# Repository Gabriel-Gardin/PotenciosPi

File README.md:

# PotenciosPi
PotenciosPi is a low cost Raspberry Pi based potenciostat. 

It uses an 12 bit ADC/DAC converter from: https://uk.pi-supply.com/products/adc-dac-pi-zero.

Schematics and the board is available at pcb folder.

To use it, install any version of Raspbian on your raspberry Pi 3 and execute Potenciostato.py

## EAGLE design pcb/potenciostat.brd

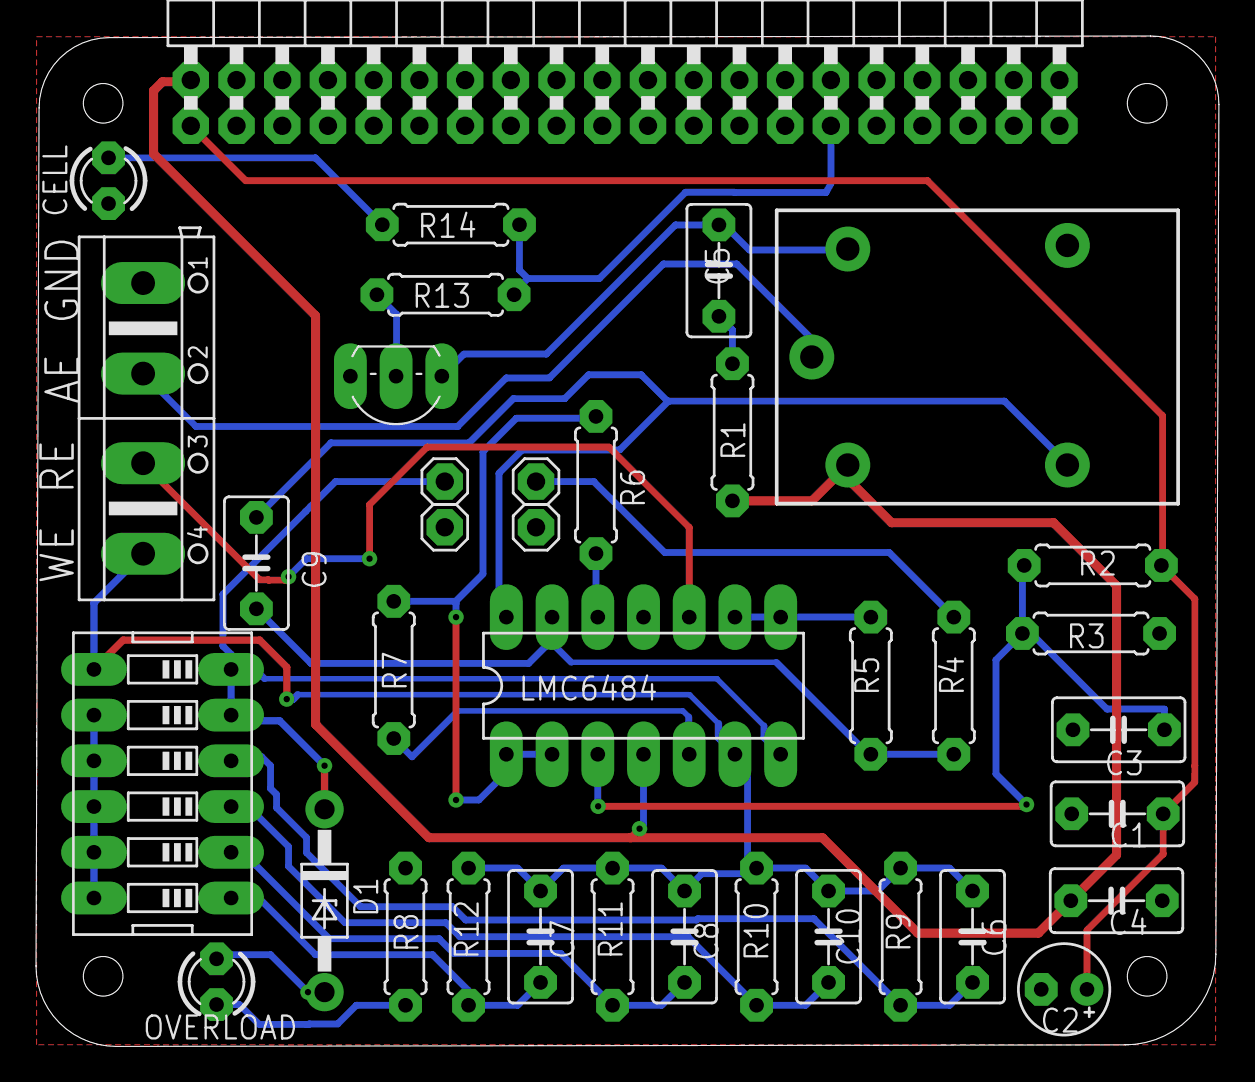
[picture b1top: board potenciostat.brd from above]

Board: 2 copper layers, 65.7 x 56.1 mm, 37 parts (0 on the bottom side), 27 nets.

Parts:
C1, C3, C4: 100nf; C050-035X075
C2: 1uF; E2,5-5
C5: ?; C050-035X075
C6, C7, C8, C10: 1uF; C050-035X075
C9: 1nf; C050-035X075
CELL: LED3MM
D1: 1N4728; DO41Z10
JP1: 2X20/90
JP2, JP3, JP4, JP5: 1X01
K2: ZNS5406; ZN5
LMC6484: TL074P; DIL14
OVERLOAD: Overload; LED3MM
Q1: BC548; TO92-EBC
R1: ?; 0207/7
R2, R3, R4, R5: 10K; 0207/7
R6, R7, R11: 4K7; 0207/7
R8: 1k; 0207/7
R9: 470K; 0207/7
R10: 47K; 0207/7
R12: 470; 0207/7
R13: 560R; 0207/7
R14: 1K; 0207/7
SW1: EDG-06
X1: AK500/4

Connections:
3V3: C1.1, C2.+, JP1.1, R2.2
5V: C4.1, JP1.2, K2.A1, LMC6484.4, R1.2
AD: D1.C, JP4.1, LMC6484.7, SW1.5, SW1.6
AUX: C9.2, K2.14, LMC6484.14
AUXEL: K2.11, X1.2
DA: JP2.1, R4.2
GND: C1.2, C2.-, C3.2, C4.2, CELL.K, JP1.25, JP1.39, JP3.1, JP5.1, LMC6484.11, Q1.E, R3.1, R8.1, X1.1
GPIO: JP1.29, R13.1, R14.1
unnamed: OVERLOAD.A, R8.2
unnamed: LMC6484.8, LMC6484.9, R5.2
unnamed: C3.1, LMC6484.3, R2.1, R3.2
unnamed: C9.1, LMC6484.13, R4.1, R5.1
unnamed: C5.1, R1.1
unnamed: LMC6484.12, R6.2
unnamed: C7.2, R12.1, SW1.1
unnamed: LMC6484.5, R7.2
unnamed: SW1.8, SW1.9, SW1.10, SW1.11, SW1.12
unnamed: D1.A, OVERLOAD.K
unnamed: C8.2, R11.1, SW1.2
unnamed: C10.2, R10.1, SW1.3
unnamed: C6.2, R9.1, SW1.4
unnamed: C5.2, K2.A2, Q1.C
unnamed: CELL.A, R14.2
unnamed: Q1.B, R13.2
REFEL: LMC6484.10, X1.3
VCC/2: LMC6484.1, LMC6484.2, R6.1, R7.1
WEL: C6.1, C7.1, C8.1, C10.1, LMC6484.6, R9.2, R10.2, R11.2, R12.2, SW1.7, X1.4

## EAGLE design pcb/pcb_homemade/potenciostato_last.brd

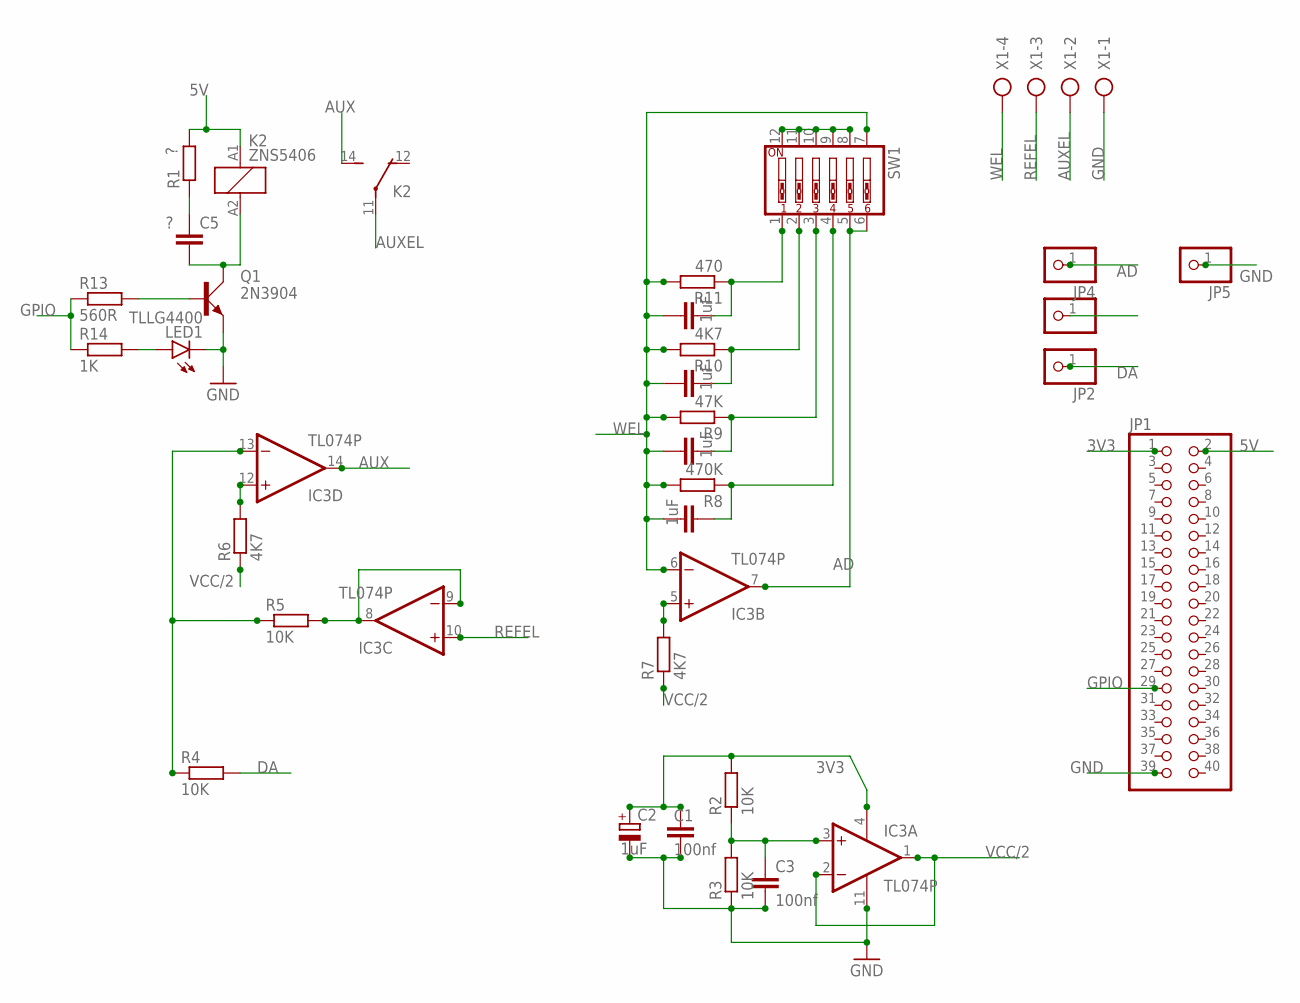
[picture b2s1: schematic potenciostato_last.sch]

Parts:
C1, C3: 100nf; C050-035X075
C2: 1uF; E2,5-5
C4, C6, C7, C8: 1uF; C050-035X075
C5: ?; C050-035X075
IC3: TL074P; DIL14
JP1: PINHD-2X20/90; 2X20/90
JP2, JP3, JP4, JP5: PINHD-1X1; 1X01
K2: ZNS5406; ZN5
LED1: TLLG4400; LED3MM
Q1: 2N3904; TO92D
R1: ?; 0207/7
R2, R3, R4, R5: 10K; 0207/7
R6, R7, R10: 4K7; 0207/7
R8: 470K; 0207/7
R9: 47K; 0207/7
R11: 470; 0207/7
R13: 560R; 0207/7
R14: 1K; 0207/7
SW1: SW_DIP-6; EDG-06
X1: AK500/4

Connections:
3V3: C1.1, C2.+, IC3.4 (V+), JP1.1, R2.2
5V: JP1.2, K2.A1 (1), R1.2
AD: IC3.7 (OUT), JP4.1, SW1.5, SW1.6
AUX: IC3.14 (OUT), K2.14 (S)
AUXEL: K2.11, X1.2
DA: JP2.1, R4.2
GND: C1.2, C2.-, C3.2, IC3.11 (V-), JP1.39, JP5.1, LED1.K (C), Q1.E, R3.1, X1.1
GPIO: JP1.29, R13.1, R14.1
unnamed: C4.2, R8.1, SW1.4
unnamed: IC3.8 (OUT), IC3.9 (-IN), R5.2
unnamed: C3.1, IC3.3 (+IN), R2.1, R3.2
unnamed: IC3.13 (-IN), R4.1, R5.1
unnamed: C5.1, R1.1
unnamed: IC3.12 (+IN), R6.2
unnamed: IC3.5 (+IN), R7.2
unnamed: SW1.8, SW1.9, SW1.10, SW1.11, SW1.12
unnamed: C6.2, R11.1, SW1.1
unnamed: C7.2, R10.1, SW1.2
unnamed: C8.2, R9.1, SW1.3
unnamed: C5.2, K2.A2 (2), Q1.C
unnamed: LED1.A, R14.2
unnamed: Q1.B, R13.2
REFEL: IC3.10 (+IN), X1.3
VCC/2: IC3.1 (OUT), IC3.2 (-IN), R6.1, R7.1
WEL: C4.1, C6.1, C7.1, C8.1, IC3.6 (-IN), R8.2, R9.2, R10.2, R11.2, SW1.7, X1.4

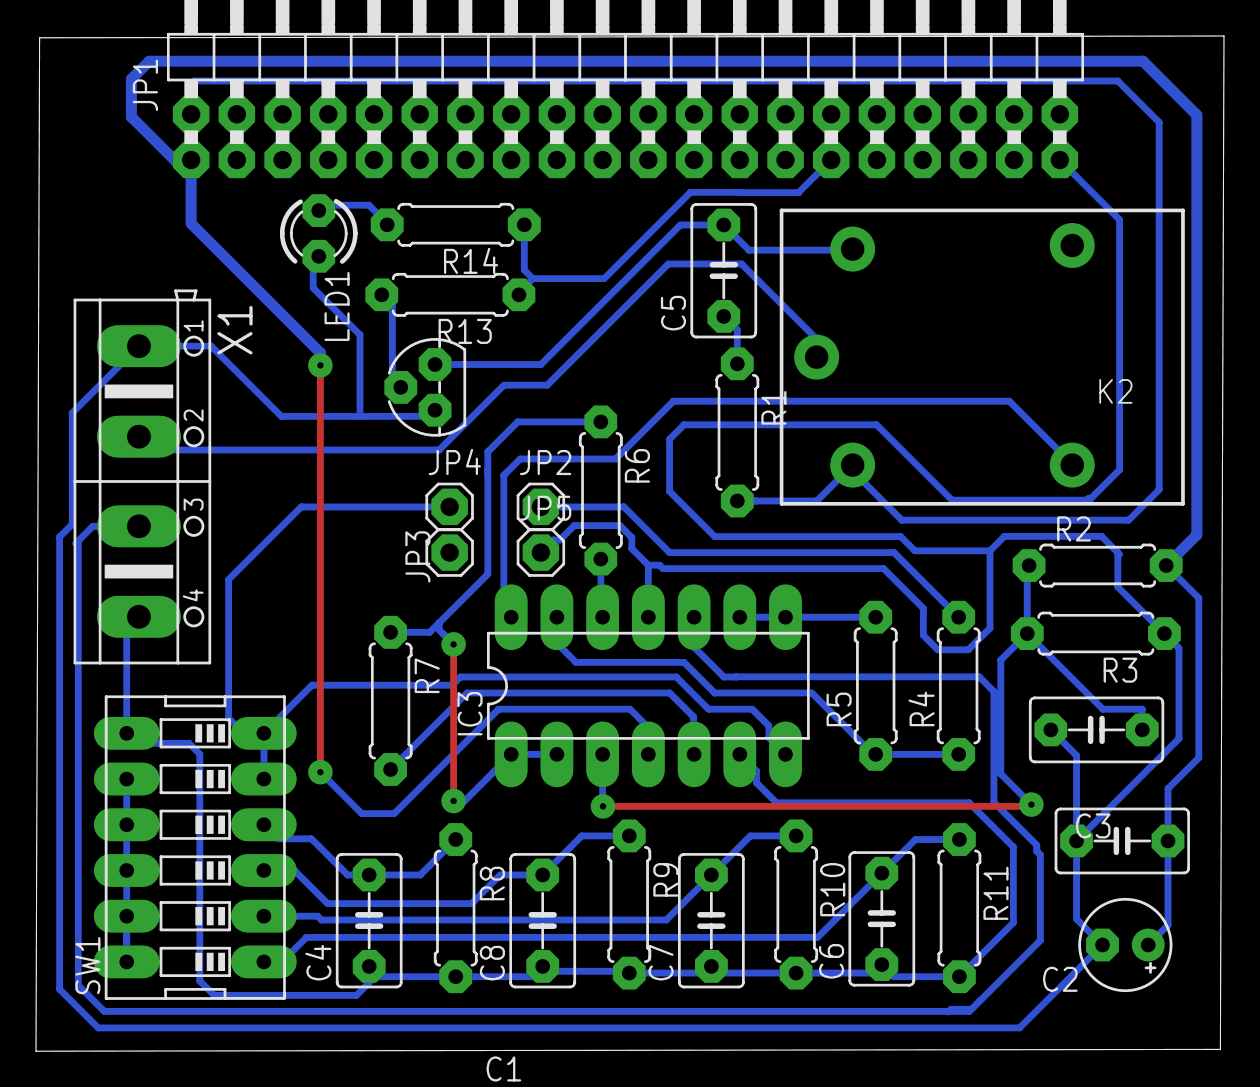
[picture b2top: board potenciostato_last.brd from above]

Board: 2 copper layers, 66.0 x 56.4 mm, 32 parts (0 on the bottom side), 25 nets.

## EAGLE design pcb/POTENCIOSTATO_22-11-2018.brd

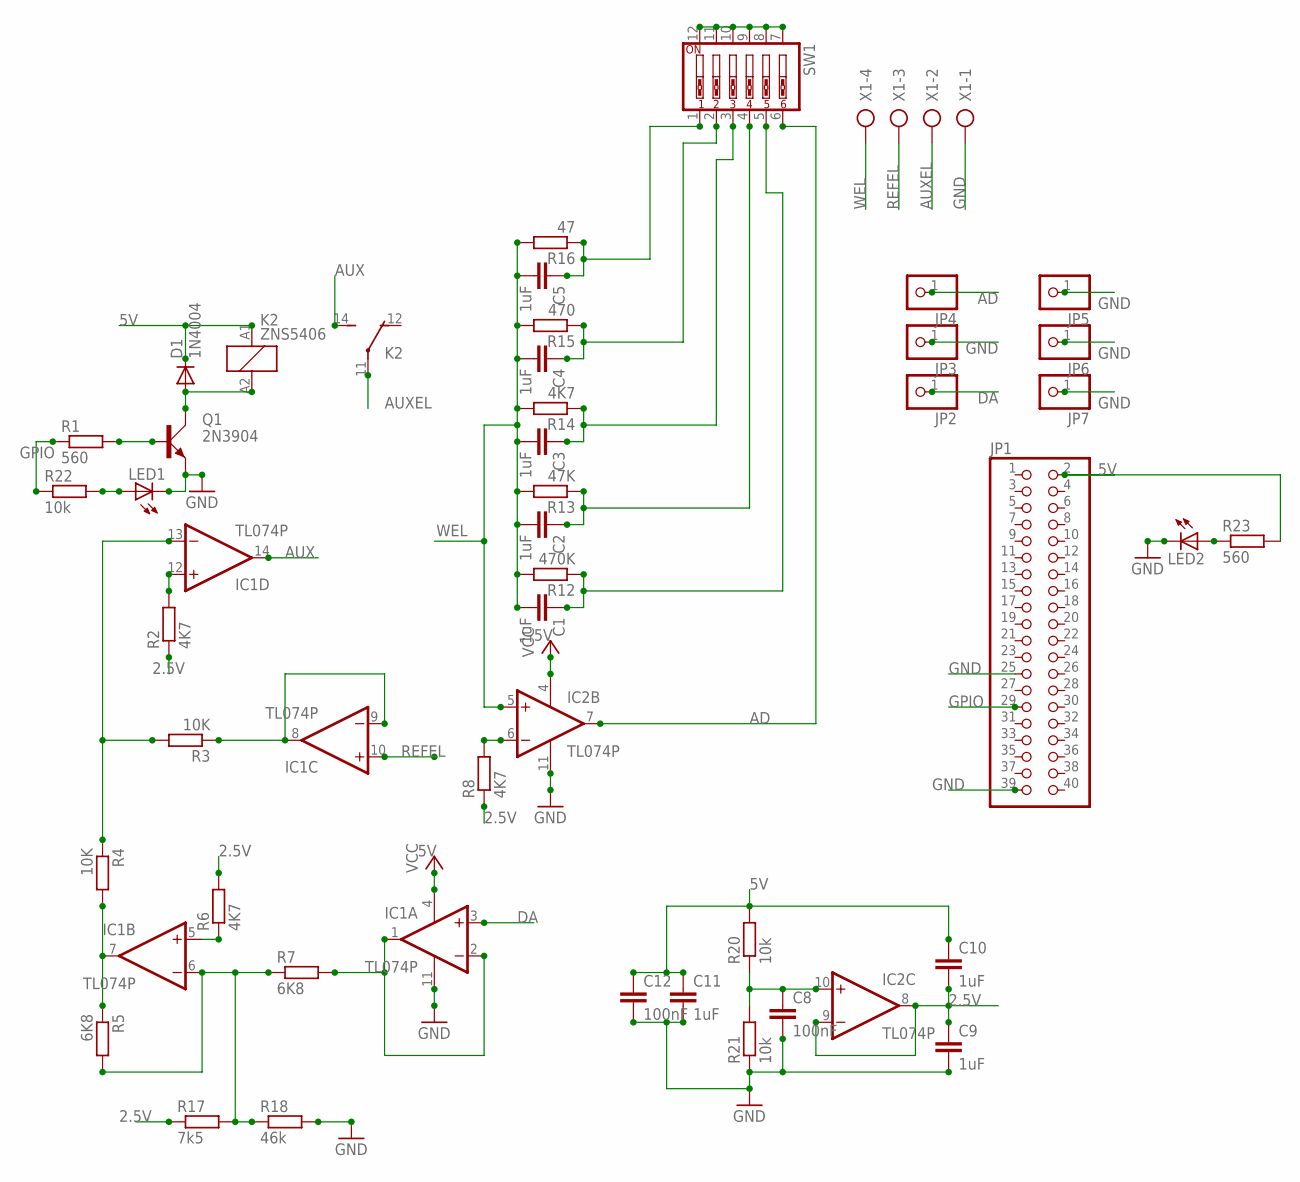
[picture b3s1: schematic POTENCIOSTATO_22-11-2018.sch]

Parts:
C1, C2, C3, C4, C5, C9, C10, C11: 1uF; C0805
C8, C12: 100nF; C0805
D1: 1N4004; DO41-10
IC1, IC2: TL074P; DIL14
JP1: PINHD-2X20/90; 2X20/90
JP2, JP3, JP4, JP5, JP6, JP7: PINHD-1X1; 1X01
K2: ZNS5406; ZN5
LED1, LED2: LEDSML0805; SML0805
Q1: 2N3904; TO92D
R1, R23: 560; R0805
R2, R6, R8, R14: 4K7; R0805
R3, R4: 10K; R0805
R5, R7: 6K8; R0805
R12: 470K; R0805
R13: 47K; R0805
R15: 470; R0805
R16: 47; R0805
R17: 7k5; R0805
R18: 46k; R0805
R20, R21, R22: 10k; R0805
SW1: SW_DIP-6; EDG-06
X1: AK500/4

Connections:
2.5V: C9.1, C10.2, IC2.8 (OUT), IC2.9 (-IN), R2.1, R6.2, R8.1, R17.1
5V: C10.1, C11.1, C12.1, D1.C, IC1.4 (V+), IC2.4 (V+), JP1.2, K2.A1 (1), R20.2, R23.2
AD: IC2.7 (OUT), JP4.1, SW1.6
AUX: IC1.14 (OUT), K2.14 (S)
AUXEL: K2.11, X1.2
DA: IC1.3 (+IN), JP2.1
GND: C8.2, C9.2, C11.2, C12.2, IC1.11 (V-), IC2.11 (V-), JP1.25, JP1.39, JP3.1, JP5.1, JP6.1, JP7.1, LED1.C, LED2.C, Q1.E, R18.2, R21.1, X1.1
GPIO: JP1.29, R1.1, R22.1
unnamed: C5.1, R16.1, SW1.1
unnamed: C4.1, R15.1, SW1.2
unnamed: C3.1, R14.1, SW1.3
unnamed: C2.1, R13.1, SW1.4
unnamed: C1.1, R12.1, SW1.5
unnamed: IC2.6 (-IN), R8.2
unnamed: SW1.7, SW1.8, SW1.9, SW1.10, SW1.11, SW1.12
unnamed: LED1.A, R22.2
unnamed: C8.1, IC2.10 (+IN), R20.1, R21.2
unnamed: D1.A, K2.A2 (2), Q1.C
unnamed: IC1.12 (+IN), R2.2
unnamed: Q1.B, R1.2
unnamed: IC1.8 (OUT), IC1.9 (-IN), R3.1
unnamed: IC1.13 (-IN), R3.2, R4.1
unnamed: IC1.7 (OUT), R4.2, R5.1
unnamed: IC1.6 (-IN), R5.2, R7.1, R17.2, R18.1
unnamed: IC1.1 (OUT), IC1.2 (-IN), R7.2
unnamed: IC1.5 (+IN), R6.1
unnamed: LED2.A, R23.1
REFEL: IC1.10 (+IN), X1.3
WEL: C1.2, C2.2, C3.2, C4.2, C5.2, IC2.5 (+IN), R12.2, R13.2, R14.2, R15.2, R16.2, X1.4

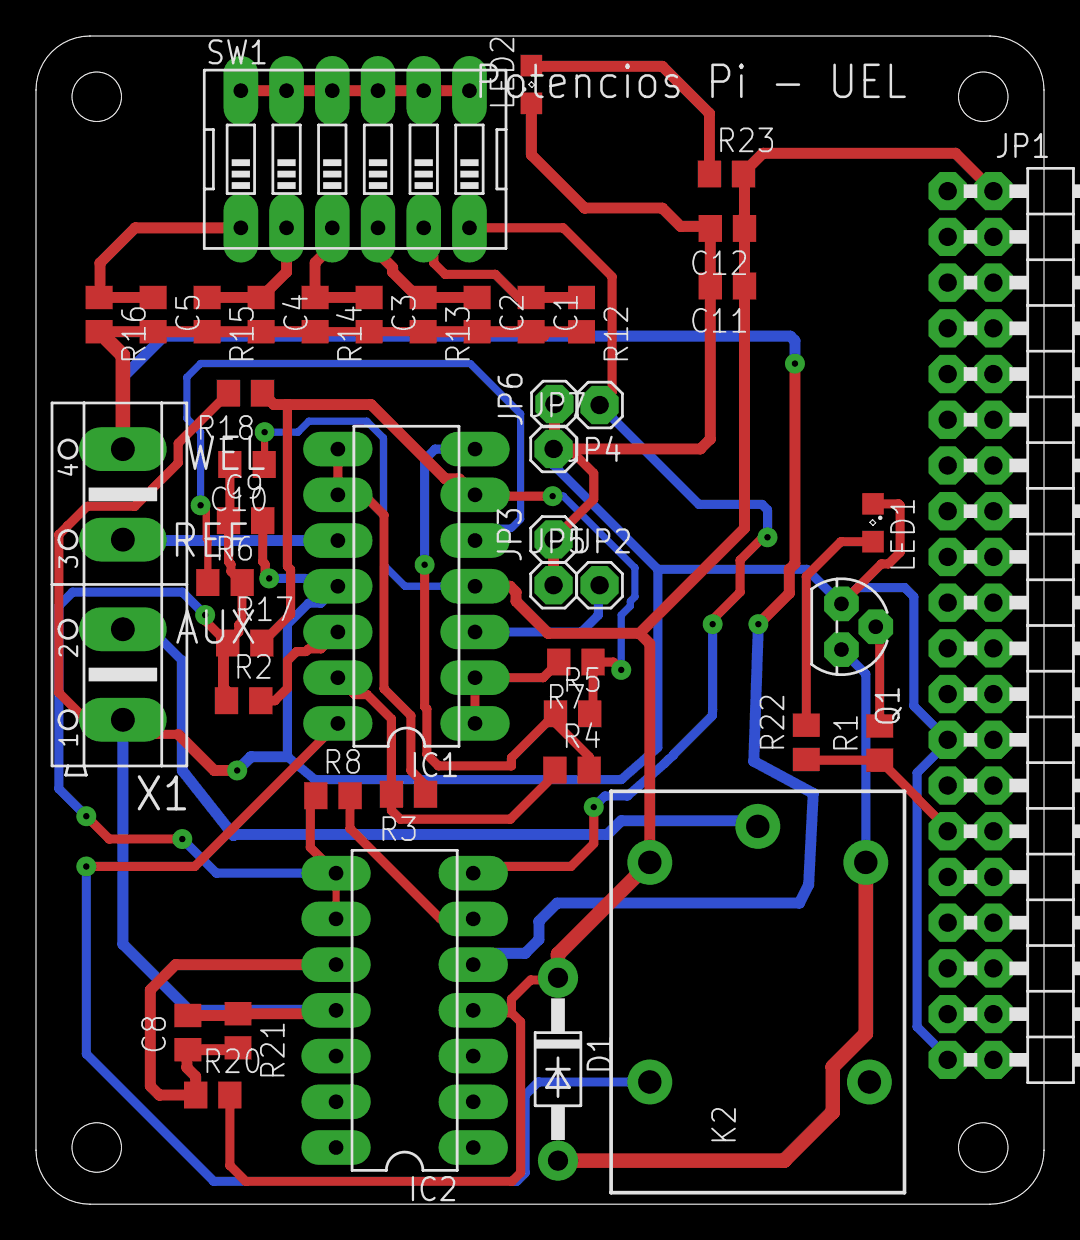
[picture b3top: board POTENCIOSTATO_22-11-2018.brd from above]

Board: 2 copper layers, 56.0 x 64.9 mm, 45 parts (0 on the bottom side), 29 nets.

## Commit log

2019-01-27 Commit Inicial
2019-01-27 Commit que retirou arquivos desnecessários
2019-01-28 Adicionei o arquivo .gitignore
2019-01-29 Inclui arquivos atualizados da pcb assim como os arquivos gerber.
2019-01-29 Trabalhando diretamente com o arquivo .ui
2019-01-29 Deletei arquivo redundante da PCB .zip
2019-01-30 Carregamento dos arquivos ui das diferentes janelas funcionando. Exit box adicionado
2019-01-31 Atualização da pcb. Versão final
2019-01-31 Carregamento dos arquivos ui e troca entre janelas pronto
2019-01-31 Alterações no modo de reescrever método de fechar a janela
2019-02-01 Pequenas alterações na função run
2019-02-04 Adicionando funções aos botoes
2019-02-04 Promote Qgraphics view to pyqtgraph class
2019-02-04 Promoted class to pyqtgraph
2019-02-04 Conectei funções aos botões falta fazer o botão stop
2019-02-06 Botão de parar a voltametria funcionando
2019-03-18 Adicionei a janela Calibrate
2019-03-18 GUI calibrar alterada
2019-03-18 Adicionei funções de calibrar, falta exportar o json
2019-03-21 Calibrar funcionando
2019-04-24 Final Board WIP
2019-04-29 Final_version, imprimir layout para confirmar
2019-04-29 Final_version, imprimir layout para confirmar WIP
2019-04-30 Correções no AD/DA e na aquisição de pontos
2019-04-30 Correções no AD/DA e na aquisição de pontoss
2019-05-03 Finalizada versão homemade. Utiliza ADC/DAC 2 da placa.
2019-05-24 Add auto calibrate
2019-05-24 Quase lá
2019-05-28 Add visualizador de dados
2019-05-30 Multi scan e visualizer
2019-05-30 wdwdw
2019-05-31 Switch to master
2019-07-26 PCB update
2019-08-04 Remove prints and add docstrings
2019-09-30 Corrigi pad do ad
2019-10-30 Placa com seleção ganho
2019-10-31 Rastnet
